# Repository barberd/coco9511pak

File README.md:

# CoCo Am9511 Pak

## Description

This board is a cartridge for the Tandy Radio Shack TRS-80 Color Computer (CoCo), an 8 bit computer produced between 1980 and 1991. It provides an Arithmetic Processor Unit (APU), the AMD 9511, to the CoCo.

Note the specific component value for X1 on the board's markings and the bill of materials is for the Am9511-4DC; see below if one has a different chip.

Schematic is available [here](kicad/coco9511pak.pdf).

A software patch for the Color Computer 3's BASIC can be found in the [Basic Patch](Basic%20Patch/) directory.

## How to order for fabrication

Download [kicad/coco9511pak-fabrication.zip](kicad/coco9511pak-fabrication.zip), then upload it to one's PCB manufacturer when asked to provide Gerber files. Usually this is found under a 'Quote' option on the website. Search "pcb manufacturing" on any major search engine to get several manufacturers. NextPCB and PCBWay are two well-known ones.

Some may have ordered boards and have extra available. Reach out to don &#x40; dgb3.net to explore this.

Use the [Bill of Materials](kicad/coco9511pak.csv) to source the components from electronic supply houses such as Mouser, Jameco, or Digi-Key.

## Source and License

Design maintained at [https://github.com/barberd/coco9511pak](https://github.com/barberd/coco9511pak). [Kicad](https://www.kicad.org/) and [Freerouting](https://github.com/freerouting/freerouting/) were used to design the board.

The design is copyright 2023 by Don Barber. The design is open source, distributed via the GNU GPL version 3 license. Please see the COPYING file for details.

## Why

The Am9511 chip provides 16 bit and 32 bit fixed point and 32 bit floating point arithmetic, including ADD, SUB, MUL, DIV, SIN, COS, TAN, ASIN, ACOS, ATAN, EXP, PWR, SQRT, LN, and supporting functions (such as fixed to float conversions). Such functions are often slower for 8 bit processors to calculate, so developers can offload such processing to the Am9511, where it can be done faster. Additionally, the main CPU may continue to do other activities while the APU works in parallel.

For example, a hardware floating point divide can take up to 184 clock cycles (92,000 nanoseconds at 2 Mhz) on the Am9511, but may take over 13,000 cycles (6,500,000 nanoseconds at 2 Mhz) using just the CPU, making floating point math on the Am9511 about 70x faster. Additionally, a 4 Mhz clock can be used on the Am9511-4DC, making it even faster.

This is often used for technical or scientific uses where very fast arithmetic is desirable. For example, see [NASA Technical Memorandum TM-86517](https://archive.org/details/NASA_NTRS_Archive_19850026198/page/n1/mode/2up) from July 1985 for a description on how NASA used these chips for controlling structural vibrations, and needed all the computations done within 20ms. They actually put four Am9511s in parallel! (Note the 6502 processor used in that memo has the opposite BCC/BCS behavior compared to the 6809; keep this in mind when reviewing Figure 6 on page 15; the 'BCS BA4' should be 'BCC BA4' when transcoding to the CoCo.)

A quick benchmark executing in [Basic](Basic%20Patch/) that loops over Y=(TAN(ATN(SQR(Y\*Y)))+1)/Y 368 times gets these results:

 * Stock CoCo3: 66.08 seconds
 * CoCo3 with "Poke 65497,0" double speed poke: 32.86 seconds
 * CoCo3 with Am9511-4 and Basic Patches: 5.95 seconds
 * CoCo3 with Am9511-4, Basic Patches, and Double Speek Poke: 3.5 seconds

So, use of the Am9511 results in about 10x speed in floating-point operations when compared to the algorithms in the built-in Basic ROM. Please note this is linear, as the CPU waits for the result while the Am9511 is processing. A program that does other work in parallel could see even faster results. Compiled code or code written in machine language should see even larger increases; somewhere between 10x and 70x performance depending upon the activity.

### More on the APU

Intel licensed the Am9511 design and produced it as the 8231. AMD also produced the 9512, which is pin compatible and provides 64 bit arithmetic, but only supports ADD, SUB, MUL, and DIV. The AM9512 was also licensed by Intel as the 8232. This pak should support all of them.

The APU may also be referred to as a floating-point unit (FPU) or a math coprocessor. The latter is a misnomer however; math coprocessors work in tandem with a CPU by extending the instruction set, such as the 387 for the Intel 386 CPU or the MC68882 for the 68k CPU. The Am9511 is better thought of as an IO peripheral, in that software instructs the CPU to output data and commands to it, then inputs the results later.

## Using the Board

### Configuration

Set the 6 dip switches (SW1) for the desired base IO address. These correspond to address lines A2 through A7. The default is $FF70 (switches set to 011100), which generally should not have a conflict unless one has configured another hardware device with a conflicting IO address. See [here](https://www.cocopedia.com/wiki/index.php/External_Hardware_IO_Address_Map) for a list of known IO hardware addresses.

The orientation of SW1 matters; it should be that the 'circuit is closed' or 'on' direction points to the 0 side. This is because the 74LS682 chip works by defaulting to '1' unless pulled to ground to make it a '0'. This simplifies and lowers the cost of the address selection circuit but also results in the non-intuitive use of 'on' to get a '0' instead of a '1'.

As such, make sure to orient the switch to match 'on' to face the same direction as the '0' label. If one gets the switch upside down, not a big deal, the switch will just operate in reverse from the silkscreened labels.

Board versions 1.2 and later reversed the earlier locations of the '0' and '1' labels as most (but not all) switches on the market were printed in such a way they had to be installed upside down. This is completely arbitrary and only done for aesthetic reasons.

### Overview

The four addresses used correspond to different registers on the Am9511 and board. For example, if given base address of $FF70:

  * $FF70 Data Register (Read and Write)
  * $FF71 Command Register (Write) and Status Register (Read)
  * $FF72 Latch Register (Read)
  * $FF73 Mirror of Latch Register

Read the [Am9511 Datasheet](docs/9511%20Datasheet.pdf?raw=true), [Algorithm Details for the Am9511 Arithmetic Processing Unit](docs/The%20Am9511%20Arithmetic%20Processing%20Unit.pdf?raw=true), and the [Am9511A/Am9512 Floating Point Processor Manual](docs/Am9511A-9512FP_Processor_Manual.pdf?raw=true) for how to use the chip. The only adjustment for this board is that instead of reading directly from the chip, a two-step read is needed. The first will read the data into a latch, and a second read will load the real data into the CPU. See the Implementation Details below for information on why this is needed.

### Examples

For example, to perform a float multiply:

	 	LDX	#fpbuf1+4		End of Floating Point Buffer 1
		LDY	#fpbuf2+4		End of Floating Point Buffer 2
		LDU	#result			Result Buffer
		LDB	#4
	loop1	LDA	,-X			Push Buffer 1 contents into chip
		STA	$FF70
		DECB
		BNE	loop1	
		LDB	#4
	loop2	LDA	,-Y			Push Buffer 2 contents into chip
		STA	$FF70
		DECB
		BNE	loop2
		LDA	#$12			Load in FMUL instruction
		STA	$FF71			and send to chip's command register
		;
		;
		; The software/CPU can now go off to do other things while the
		; APU performs this command. FMUL can take up to 168 cycles.
		; Or one can continue straight to the status check loop and 
		; wait for the APU to finish.
		;
		;
	loop3	LDA	$FF71			Read from status register into latch
		;CPU will halt here until data is read
		LDA	$FF72			Now read from latch
		BMI	loop3			If bit 7 (Busy) is high, then loop
		LDB	#4
	loop4	LDA	$FF70			Pop result from chip into latch
		;CPU will halt here until data is read
		LDA	$FF72			Read from latch
		STA	,U+			Store into result buffer
		DECB
		BNE	loop4

### Interrupts

Optionally, to trigger an interrupt when a command is complete, issue the command to the Am9511 with bit 7 high. For example, use $93 for FDIV instead of $13. See the Am9511 datasheet for details. Using interrupts enables programs go on to other work and return once the command is complete without needing to poll for a status change.

Commands with bit 7 high will cause the Am9511's SVREQ pin to go high when complete, which causes a 74LS05 (an open-collector NOT gate) to pull the cartridge's pin 8 (CART\*) low. This pin will stay low until the service request is acknowledged by reading from the chip. When PIA1 is configured to do so, a fast interrupt request is sent to the CPU when CART\* goes low.

To configure the PIA1 to do this, enable fast interrupts and configure it to trigger on a falling edge, like so:

                LDA     $FF23           ;load PIA1 Side B Control Register
                ORA     #$01            ;set bit 0 to 1 to enable cart firq
                ANDA    #$FD            ;set bit 1 to 0 to trigger on falling-edge
                STA     $FF23           ;store in PIA1 Side B Control Register

Hook in the interrupt handler at $010F (and/or $FEF4 on the CoCo3) as one would any other FIRQ handler. Make sure the interrupt handler performs a SVACK through a chip read.

## Implementation Details

Interfacing the Am9511 to the Color Computer is tricky. The Am9511 has a long read time; even on the fastest 4Mhz Am9511-4DC the time can range from 925ns to 1575ns. The standard Am9511, assuming its running at its fastest 2Mhz, can take from 1730 ns to 2840 ns. A standard Color Computer running at .89 Mhz has a clock cycle of 1117ns, with the needed lines only valid for 488ns of that. On a Color Computer 3 with the double speed poke, this becomes only 244ns. As such, the Am9511 read time takes longer than the CoCo listens for a response.

This problem of the Am9511 read time taking longer than a CPU clock cycle is not unique to the Color Computer (a CPU would have to be running at about 0.3Mhz to ensure an Am9511 read fits into a clock cycle, and CPUs were already faster than this when it came out). To account for this, many 8 bit CPUs either have a READY line available for peripherals to hold the CPU in the middle of an instruction (the 8080, Z80, and 6502 CPUs for example), or there is another way to pause the CPU's clock (using a 6871A clock chip with a 6800 for example). However, neither is available on the Color Computer, at least not without hardware modification.

As such, this pak uses a 74LS374 latch register accessible at a third IO address to store read data coming from the Am9511. Software reading from the chip needs to perform two instructions: one to instruct the Am9511 to copy its data to that register, and another for the CPU to load from the register. The CPU HALT line is used to pause the CPU at the end of the first load instruction until the transfer is complete, so the data is always ready in time for the second instruction.

For example, to check the status register:

		LDA	$FF71	Load the status register into the latch register
		; CPU halts here until the data is loaded into the latch
		; The above 'LDA' pulls in junk data, just ignore it and use the below
		; 'LDA' to pull in the real data
		LDA	$FF72	Load the actual status result from the latch register into CPU 'A' register

For another example, to pull 4 bytes off the Am9511's data register stack:

		LDX	#outputbuffer
		LDB	#4
	loop	LDA	$FF70	Read from data register into latch
		;CPU will halt here until data is read
		LDA	$FF72	Then read the real data	
		STA	,X+	And store it into the buffer
		DECB
		BNE	loop

This 'two instructions to read' method may not be the most elegant for those used to programming the Am9511 on an 8080, but was necessary due to the timing considerations discussed above. An alternative, if one wants to design their own board, is to use a PIA, discussed below.

Additionally, when doing a write, the Am9511-4 and Am9511-1 needs the write line to complete 30 ns (60 ns for the Am9511) before the chip select is finished. Since both signals are normally derived from the same clock on the Color Computer, they normally finish at the same time. As such, a one-shot multivibrator 74LS123 is used; the write signal triggers the one shot that provides the needed 100 ns pulse (150 ns on the Am9511), leaving enough time in the clock cycle to meet valid data bus and chip select timing requirements. See the below section 'Write Timing' for additional detail.

### But I don't want to HALT the CPU during a read!

Jumper JP1 is included on the board design so the HALT behavior can be disabled. If disabled, then the programmer will need to account for the time it takes for chip transfer to complete instead by calculating software instruction timing. 

On a 6809 CoCo running at .89 Mhz this is not an issue and the jumper can be removed to disable the HALT behavior; a LD instruction takes three cycles so the time for the two intervening clock cycles between the load cycles of the LD instructions is greater than the required 2840 ns.

However, when running without the jumper and the CoCo3 double speed poke or a 6309 processor running in native mode (so LD instructions only take 2 cycles), there might not be enough time for the transfer to complete, and the programmer will need to add in NOP instructions or perform other work to obtain the necessary timing between the two load instructions.

## Alternative Implementation Methods

Many implementers avoid the complex bus timing requirements of the am9511 by interfacing it via a Peripherial Interface Adaptor (PIA) or Versatile Interface Adaptor (VIA), such as the Intel 8225, the Motorola 6821, or the MOS 6522. This makes for a much simpler hardware interface with a tradeoff for more complex software, as the software must now 'bit-bang' the individual control lines for the 9511 chip, also taking up additional CPU cycles.

Here are a few examples:

* [Compute! Magazine Nov 1980 Interfacing the Am9511 Arithmetic Processing Unit](https://archive.org/details/1980-11-compute-magazine/page/n123/mode/2up), Page 122

* [NASA Technical Memorandum 91 for calculating magnetic variation, March 1984](https://archive.org/details/NASA_NTRS_Archive_19840012438) No hardware schematic, but does have a block diagram and the software listings

* [S100Computers.com Math Board](http://s100computers.com/My%20System%20Pages/Math%20Board/Math%20Board.htm) This one controls only the C/D line with a PIA, but otherwise is a fairly standard implementation using the 8080/Z80's READY line.

* [Micro! Aug 1981 MICROCRUNCH: An Ultra-fast Arithmetic Computing System](https://archive.org/details/sim_micro_1981-08_39/page/n7), Page 7. This one uses the two flip-flops in a 74LS76 chip like a PIA to control the R/W\* and C/D\* lines. Part 2 is in [Micro! Sep 1981](https://archive.org/details/sim_micro_1981-09_40/page/82/mode/2up), Page 83. This one uses a 74123 for writing timing much like this board.

## Providing 12 Volts

Use Jumper JP2 to select the source of 12 volts needed for the Am9511.

The original Color Computer and many Multi-Pak Interfaces (MPIs) provide +12v on the second cartridge pin. However, the CoCo 2, Coco 3, and many third-party MPIs do not provide 12 volts on this pin, so a 5v to 12v boosting circuit is included on the board design. Set JP2 to 'Circuit' to use this circuit.

But if one has a setup that provides +12v to the cartridge and wants to use this source instead, set JP2 to 'Cart.' One can then also eliminate C3, C16, C17, L1, D1, R5, R6, R7, and U3. The LT1373 (U3) and similar switching regulators can be expensive.

Alternatively, one could wire in an external 12v supply, such as a barrel connector to plug in a 12v wall transformer. Connect the +12v to a trace connected to the JP2 jumper, such as the positive side of C17, D1, or R5. Connect ground to any ground connection, such as U3's pin 5 or 6. According to the Am9511's datasheet, a supply current of 50mA is typical for the 12v input but may pull up to 90mA.

## Chip Considerations

The markings on the board and the bill of materials is for the Am9511-4DC running at 4Mhz. If one uses a 2Mhz or 3Mhz Am9511 instead, make these adjustments:

Am9511:
* X1 2Mhz Oscillator

Am9511-1:
* X1 3Mhz Oscillator

## Tuning Write Timing

For C15 and R2, if one doesn't have the exact values on hand, one can use a larger capacitor with a smaller resistor (and visa-versa). One is trying to get the pulse to be long enough to meet the TDW (Data Bus Stable to WR\* High Set up Time) requirement but also short enough to allow the Am9511's TWCD (WR\* High to CS\* High Hold Time) requirement in the remaining CPU clock cycle. The range for the ideal pulse length is between 150 and 184 ns as this gives enough TDW time for the slower Am9511 but also leaves enough remaining TWCD time with the Color Computer's double speed poke. There is more flexibility if one has the Am9511-1 or Am9511-4; a pulse time between 100 and 214 ns will work, and even more flexibility if using the Am9511-1 or Am9511-4 without the double speed poke as the pulse can be anywhere between 100 and 458 ns.

See the 74LS123 datasheet and [Texas Instruments Designing With the SN54/74LS123](https://www.ti.com/lit/an/sdla006a/sdla006a.pdf) Page 3 for guidance on choosing the capacitor and resistor values. If one has a picky AM9511 one might have to check the signal timings with an oscilloscope or logic analyzer and adjust C15 and/or R2.

## More Info

Links:

* [Older Datasheet including command details](docs/Am9511%20Arithmetic%20Processor.pdf?raw=true)
* [New Datasheet with Am9511-4 timings](docs/9511%20Datasheet.pdf?raw=true)
* [Algorithm Details](docs/The%20Am9511%20Arithmetic%20Processing%20Unit.pdf?raw=true)
* [Am9511/Am9512 Processor Manual](docs/Am9511A-9512FP_Processor_Manual.pdf?raw=true) Includes schematics for interfacing to various processors including 8080, Z80, 6800, etc.
* [Color Computer Technical Reference](https://colorcomputerarchive.com/repo/Documents/Manuals/Hardware/Color%20Computer%20Technical%20Reference%20Manual%20%28Tandy%29.pdf) See Page 18 of the manual/25 of the PDF for bus timings.

## Errata

Version 1.0 of the board has several flaws and should not be used.

Version 1.1 of the board was missing two silkscreen labels (the 74LS08 and the 74LS244).

Version 1.2 switched the locations of the '0' and '1' labels on SW1 compared to earlier versions. This is arbitrary and only done because this way allows most switches on the market to be installed with their printing 'up' instead of 'down.'

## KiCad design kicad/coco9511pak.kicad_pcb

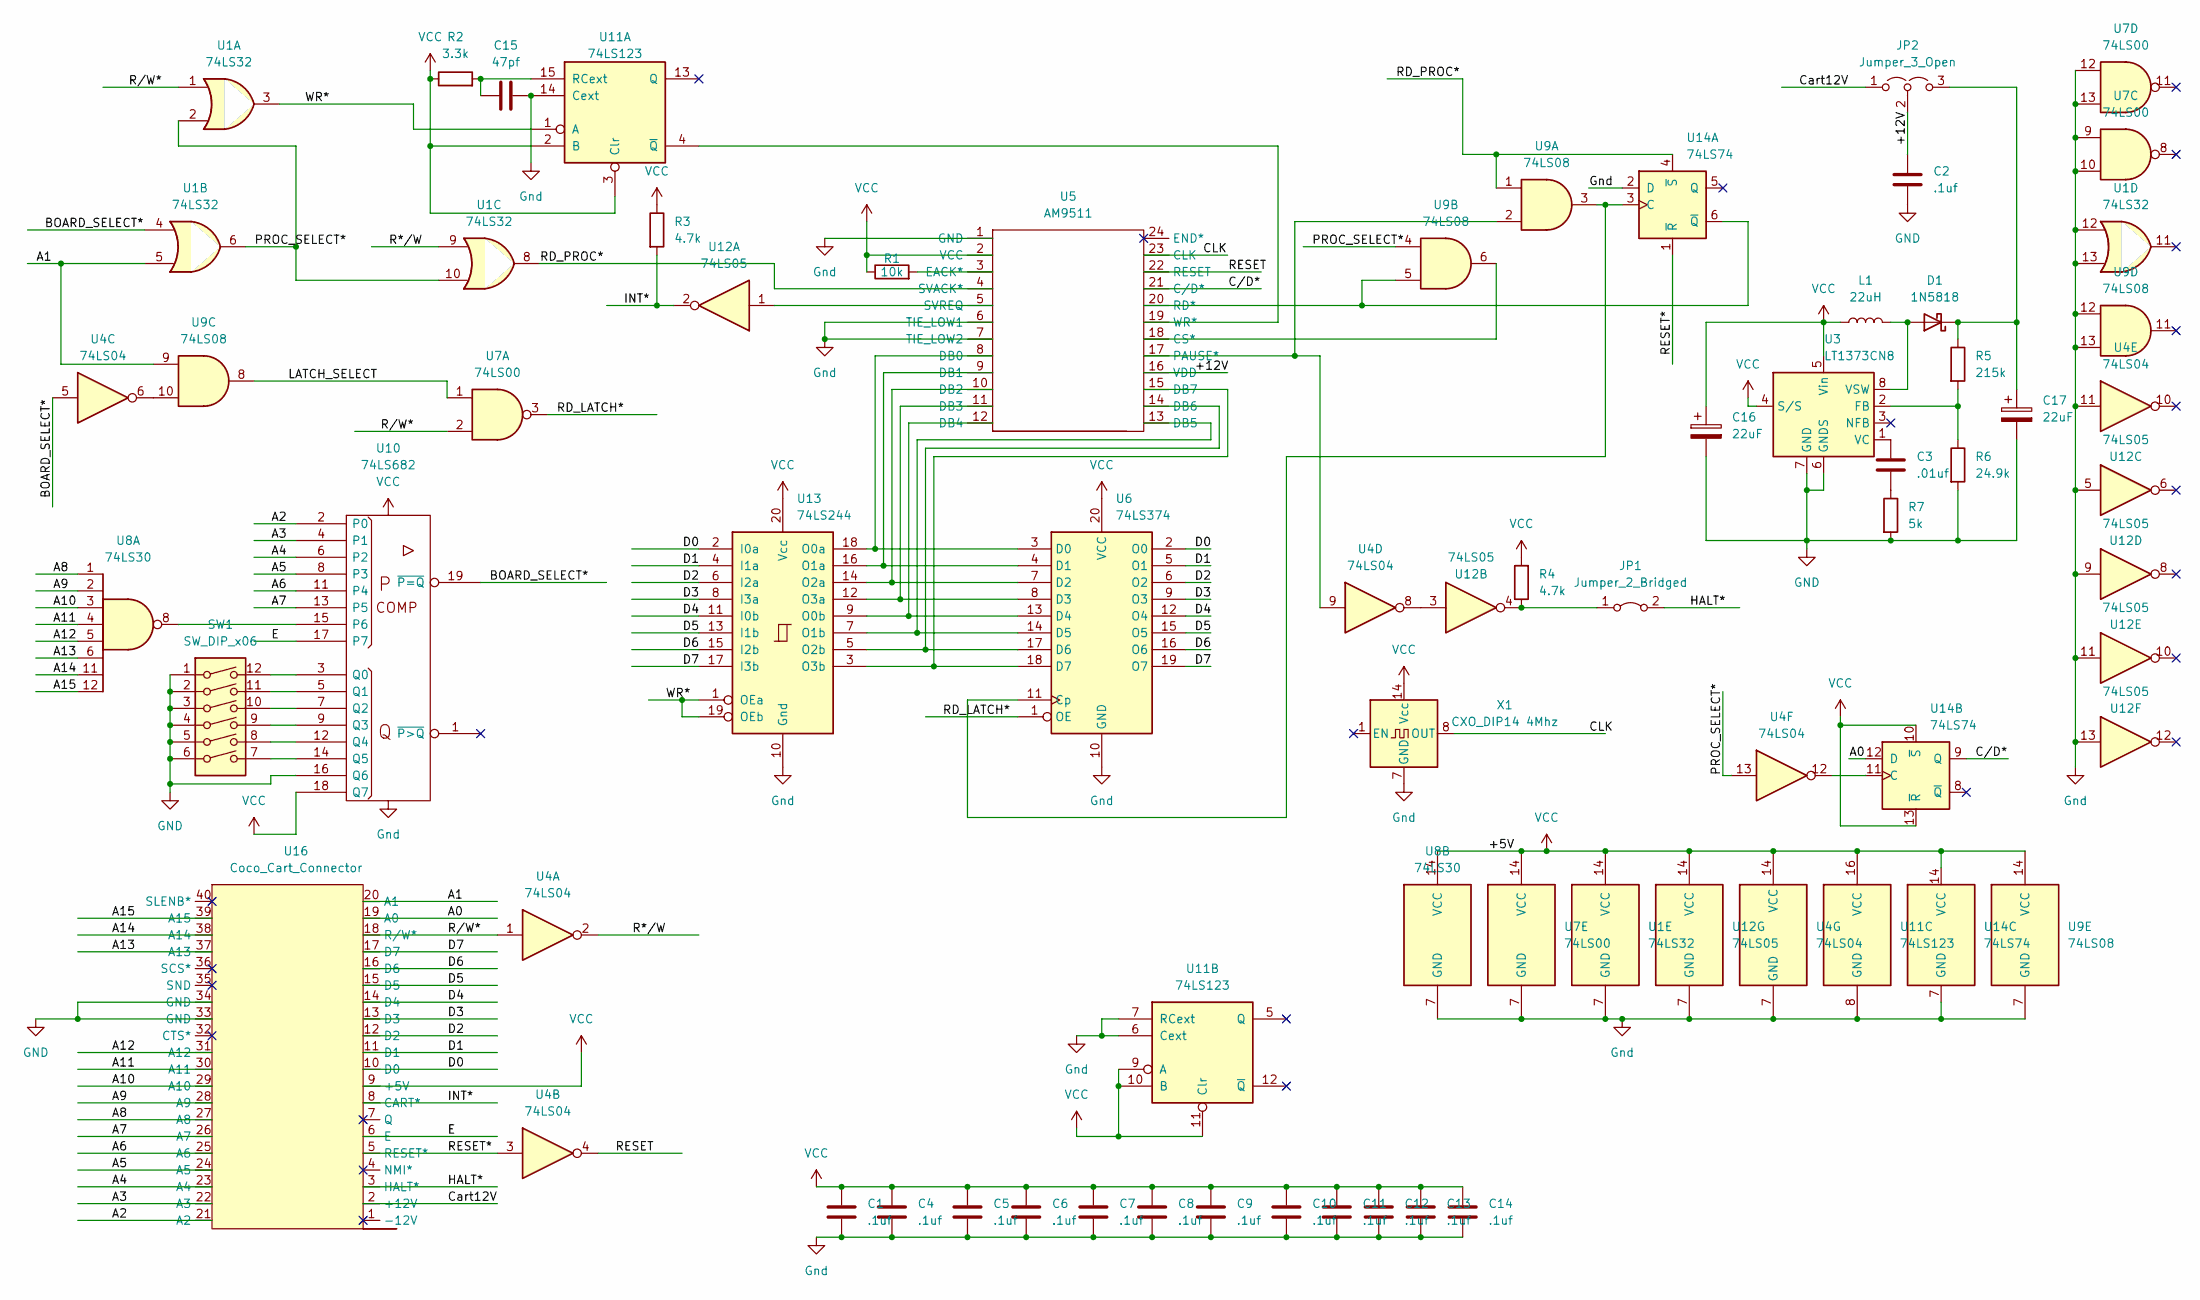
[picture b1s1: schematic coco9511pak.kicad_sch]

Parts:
C1, C2, C4, C5, C6, C7, C8, C9, C10, C11, C12, C13, C14: .1uf; C_Axial_L3.8mm_D2.6mm_P7.50mm_Horizontal
C3: .01uf; C_Axial_L3.8mm_D2.6mm_P7.50mm_Horizontal
C15: 47pf; C_Axial_L3.8mm_D2.6mm_P7.50mm_Horizontal
C16, C17: 22uF; CP_Radial_D6.3mm_P2.50mm
D1: 1N5818; D_DO-41_SOD81_P10.16mm_Horizontal
JP1: Jumper_2_Bridged; PinHeader_1x02_P2.54mm_Vertical
JP2: Jumper_3_Open; PinHeader_1x03_P2.54mm_Vertical
L1: 22uH; L_Axial_L7.0mm_D3.3mm_P10.16mm_Horizontal_Fastron_MICC
R1: 10k; R_Axial_DIN0207_L6.3mm_D2.5mm_P7.62mm_Horizontal
R2: 3.3k; R_Axial_DIN0207_L6.3mm_D2.5mm_P7.62mm_Horizontal
R3, R4: 4.7k; R_Axial_DIN0207_L6.3mm_D2.5mm_P7.62mm_Horizontal
R5: 215k; R_Axial_DIN0207_L6.3mm_D2.5mm_P7.62mm_Horizontal
R6: 24.9k; R_Axial_DIN0207_L6.3mm_D2.5mm_P7.62mm_Horizontal
R7: 5k; R_Axial_DIN0207_L6.3mm_D2.5mm_P7.62mm_Horizontal
SW1: SW_DIP_x06; SW_DIP_SPSTx06_Slide_9.78x17.42mm_W7.62mm_P2.54mm
U1: 74LS32; DIP-14_W7.62mm
U3: LT1373CN8; DIP-8_W7.62mm
U4: 74LS04; DIP-14_W7.62mm
U5: AM9511; DIP-24_W15.24mm
U6: 74LS374; DIP-20_W7.62mm
U7: 74LS00; DIP-14_W7.62mm
U8: 74LS30; DIP-14_W7.62mm
U9: 74LS08; DIP-14_W7.62mm
U10: 74LS682; DIP-20_W7.62mm
U11: 74LS123; DIP-16_W7.62mm
U12: 74LS05; DIP-14_W7.62mm
U13: 74LS244; DIP-20_W7.62mm
U14: 74LS74; DIP-14_W7.62mm
U16: Coco_Cart_Connector; Coco_Cart
X1: CXO_DIP14 4Mhz; DIP-14_W7.62mm

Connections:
/+12V: C2.1, JP2.2 (C), U5.16 (VDD)
/A0: U14.12 (D), U16.19 (A0)
/A1: U1.5, U9.9, U16.20 (A1)
/A2: U10.2 (P0), U16.21 (A2)
/A3: U10.4 (P1), U16.22 (A3)
/A4: U10.6 (P2), U16.23 (A4)
/A5: U10.8 (P3), U16.24 (A5)
/A6: U10.11 (P4), U16.25 (A6)
/A7: U10.13 (P5), U16.26 (A7)
/A8: U8.1, U16.27 (A8)
/A9: U8.2, U16.28 (A9)
/A10: U8.3, U16.29 (A10)
/A11: U8.4, U16.30 (A11)
/A12: U8.5, U16.31 (A12)
/A13: U8.6, U16.37 (A13)
/A14: U8.11, U16.38 (A14)
/A15: U8.12, U16.39 (A15)
/BOARD_SELECT*: U1.4, U4.5, U10.19 (~P=Q)
/CLK: U5.23 (CLK), X1.8 (OUT)
/Cart12V: JP2.1 (A), U16.2 (+12V)
/C/D*: U5.21 (C/D*), U14.9 (Q)
/D0: U6.2 (O0), U13.2 (I0a), U16.10 (D0)
/D1: U6.5 (O1), U13.4 (I1a), U16.11 (D1)
/D2: U6.6 (O2), U13.6 (I2a), U16.12 (D2)
/D3: U6.9 (O3), U13.8 (I3a), U16.13 (D3)
/D4: U6.12 (O4), U13.11 (I0b), U16.14 (D4)
/D5: U6.15 (O5), U13.13 (I1b), U16.15 (D5)
/D6: U6.16 (O6), U13.15 (I2b), U16.16 (D6)
/D7: U6.19 (O7), U13.17 (I3b), U16.17 (D7)
/E: U10.17 (P7), U16.6 (E)
/HALT*: JP1.2 (B), U16.3 (HALT*)
/INT*: R3.2, U12.2, U16.8 (CART*)
/LATCH_SELECT: U7.1, U9.8
/PROC_SELECT*: U1.2, U1.6, U1.10, U4.13, U9.4
/R*/W: U1.9, U4.2
/RD_LATCH*: U6.1 (OE), U7.3
/RD_PROC*: U1.8, U5.4 (SVACK*), U9.1, U14.4 (~S)
/RESET: U4.4, U5.22 (RESET)
/RESET*: U4.3, U14.1 (~R), U16.5 (RESET*)
/R/W*: U1.1, U4.1, U7.2, U16.18 (R/W*)
/WR*: U1.3, U11.1 (A), U13.1 (OEa), U13.19 (OEb)
GND: C1.2, C2.2, C4.2, C5.2, C6.2, C7.2, C8.2, C9.2, C10.2, C11.2, C12.2, C13.2, C14.2, C15.2, C16.2, C17.2, R6.2, R7.2, SW1.1, SW1.2, SW1.3, SW1.4, SW1.5, SW1.6, U1.7 (GND), U1.12, U1.13, U3.6 (GNDS), U3.7 (GND), U4.7 (GND), U4.11, U5.1 (GND), U5.6 (TIE_LOW1), U5.7 (TIE_LOW2), U6.10 (GND), U7.7 (GND), U7.9, U7.10, U7.12, U7.13, U8.7 (GND), U9.7 (GND), U9.12, U9.13, U10.10 (Gnd), U10.16 (Q6), U11.6 (Cext), U11.7 (RCext), U11.8 (GND), U11.14 (Cext), U12.5, U12.7 (GND), U12.9, U12.11, U12.13, U13.10 (Gnd), U14.2 (D), U14.7 (GND), U16.33 (GND), U16.34 (GND), X1.7 (GND)
unnamed: C3.1, U3.1 (VC)
unnamed: C3.2, R7.1
unnamed: C15.1, R2.2, U11.15 (RCext)
unnamed: C17.1, D1.1 (K), JP2.3 (B), R5.1
unnamed: D1.2 (A), L1.2, U3.8 (VSW)
unnamed: JP1.1 (A), R4.1, U12.4
unnamed: R1.2, U5.3 (EACK*)
unnamed: R5.2, R6.1, U3.2 (FB)
unnamed: SW1.7, U10.14 (Q5)
unnamed: SW1.8, U10.12 (Q4)
unnamed: SW1.9, U10.9 (Q3)
unnamed: SW1.10, U10.7 (Q2)
unnamed: SW1.11, U10.5 (Q1)
unnamed: SW1.12, U10.3 (Q0)
unnamed: U4.6, U9.10
unnamed: U4.9, U5.17 (PAUSE*), U9.2
unnamed: U5.18 (CS*), U9.6
unnamed: U8.8, U10.15 (P6)
unnamed: U5.19 (WR*), U11.4 (~Q)
unnamed: U5.5 (SVREQ), U12.1
unnamed: U4.8, U12.3
unnamed: U5.15 (DB7), U6.18 (D7), U13.3 (O3b)
unnamed: U5.14 (DB6), U6.17 (D6), U13.5 (O2b)
unnamed: U5.13 (DB5), U6.14 (D5), U13.7 (O1b)
unnamed: U5.12 (DB4), U6.13 (D4), U13.9 (O0b)
unnamed: U5.11 (DB3), U6.8 (D3), U13.12 (O3a)
unnamed: U5.10 (DB2), U6.7 (D2), U13.14 (O2a)
unnamed: U5.9 (DB1), U6.4 (D1), U13.16 (O1a)
unnamed: U5.8 (DB0), U6.3 (D0), U13.18 (O0a)
unnamed: U6.11 (Cp), U9.3, U14.3 (C)
unnamed: U5.20 (RD*), U9.5, U14.6 (~Q)
unnamed: U4.12, U14.11 (C)

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
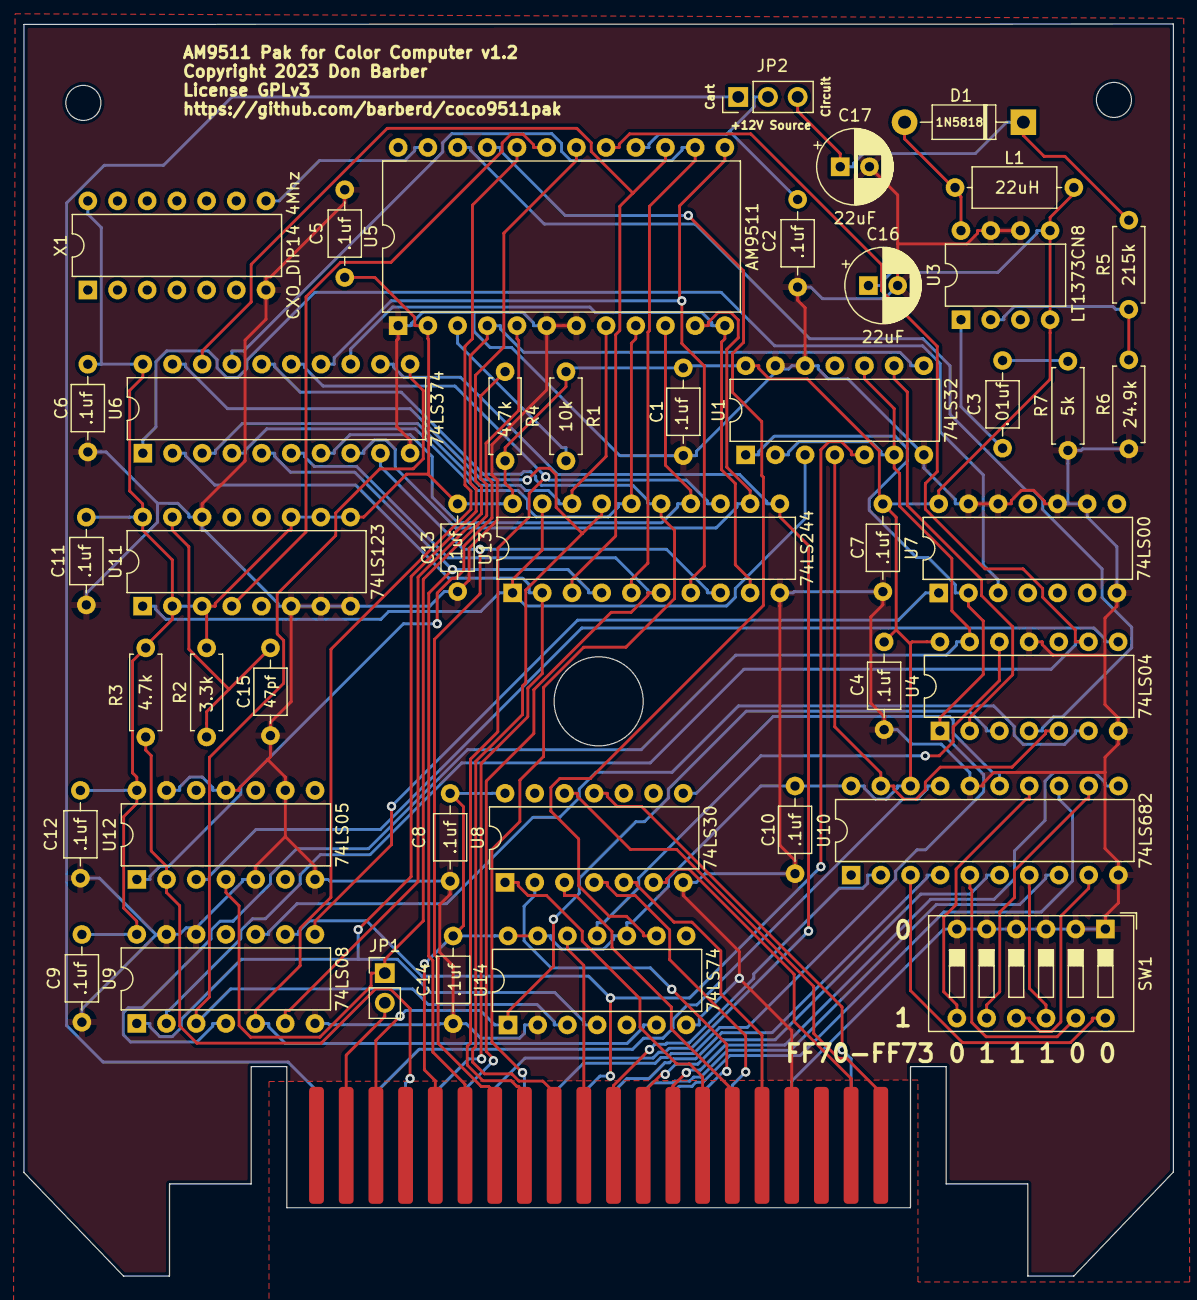
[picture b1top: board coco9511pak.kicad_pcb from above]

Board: 2 copper layers, 98.3 x 107.1 mm, 44 parts (0 on the bottom side), 75 nets.

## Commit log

2023-01-20 Formatting
2023-01-20 Added raw links
2023-01-20 Added more assembly comments
2023-01-20 Clarified
2023-01-20 Fixed link
2023-01-20 Adding photo
2023-01-20 Added image
2023-01-20 Clarified code
2023-01-20 typo
2023-01-20 Added BASIC Patch Readme
2023-01-20 typos
2023-01-20 Removed LICENSE file, using COPYING instead
2023-01-20 language
2023-01-21 Fixed comment
2023-01-24 Updated image
2023-02-04 do not order
2023-03-10 Fixed basic patch for pushing onto the 9511 stack from the end of the variable instead of the beginning
2023-03-10 Added basic benchmark
2023-03-10 Updated with benchmark
2023-03-10 fixed trailing byte in basic benchmark
2023-03-10 Phrasing
2023-03-10 Fixed basic benchmark trailing byte
2023-03-11 Updated BOM
2023-03-11 Fixed link in README
2023-03-11 Minor comment corrections
2023-03-11 Added note on U3
2023-03-11 Removed changes to display routines
2023-03-11 Clarified performance benchmark language in README
2023-03-11 Fixed typo
2023-03-11 Fixed missing vcc in boost circuit
2023-03-11 Fixed vcc in boost circuit
2023-03-13 Updated README to include discussion on interrupts
2023-03-13 Rearranged README
2023-03-15 Re-exported fabrication outputs
2023-04-11 Minor update to silkscreening
2023-04-11 Fixed readme format
2023-04-20 Added guidance for an external +12v source
2024-12-08 Contributions submitted by George Hines:
    1) Fix apu error handling to handle overflow from exp (previously it could return /0)
    2) Relocate program to $FB00 to avoid issues with basic programs that might allocate memory different (e.g. w/pclear) or conflict with loadm'ed binaries.
    3) Remove FIX as there are problems w/ints >24-bits, BASIC handles these cases and I figure that code probably isn't too slow.
    4) Fix PWR function when the argument is negative, and the exponent is an int (e.g. -2 ^ 2).
    5) Disable soft reset. Perhaps soft reset can be recoverable to reinstall the patch, but I haven't looked at it yet.
    6) A few other minor edits

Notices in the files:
kicad/coco9511pak.kicad_pcb:
Copyright 2023 Don Barber
License GPLv3
